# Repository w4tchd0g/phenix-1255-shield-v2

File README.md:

# phenix-1255-shield-v2

Expansion board (shield) for the NXP **FRDM-MCXN947** development board, built around the Semtech **SX1255** RF transceiver (TX 440 MHz, RX 430 MHz).

Together with the firmware it turns the FRDM board into a multimode SDR transceiver for base stations: TETRA today, DMR, FM and more modes planned. The I/Q samples are streamed to a host over HS USB or Ethernet.

This board is the hardware part of [phenix-1255-sw](https://github.com/w4tchd0g/phenix-1255-sw). It is **revision V2** of [phenix-1255-shield](https://github.com/w4tchd0g/phenix-1255-shield), see [Changes from V1](#changes-from-v1). Both are modified versions of [Phenix-1255-HW](https://github.com/labdvm/Phenix-1255-HW) by Z32IT ([@labdvm](https://github.com/labdvm)), see [Changes from Phenix-1255-HW](#changes-from-phenix-1255-hw).

> **Status:** V2 design complete, not yet built. The schematic passes ERC without errors, the PCB passes DRC without errors and without unrouted connections. The changes from V1 are checked by ERC/DRC and by calculation only; they still need a test on real boards. The Gerber, BOM and position files for JLCPCB and PCBWay are in [`production/`](#fabrication). Before the first power-up, read the [bring-up checklist](#bring-up-checklist).

## Preview

| Top | Bottom |
|---|---|
|  |  |

## Changes from V1

V2 continues [phenix-1255-shield](https://github.com/w4tchd0g/phenix-1255-shield) (V1). The circuit concept, the MCU pin assignment and the board outline are unchanged, so V1 firmware runs on V2 without changes (V2 also reports [hardware ID 0](#assembly-notes)). The changes (2026-11) are:

**RF front end**

- **RX SAW filter:** Tai-Saw TA1651A (428 MHz, passband 420–436 MHz, 3.0 × 3.0 mm, LCSC C5224551) instead of the Tai-Saw TA0655A (430 MHz, 4 MHz passband). JLCPCB places it; the TA0655A had to be soldered by hand. It rejects ≥ 45 dB below 400 MHz and above 470 MHz, but only about 2 dB more than in the passband at 439–440 MHz (the upper edge), so it does not reject the TX signal; for duplex operation an external duplexer at J5/J6 provides the TX/RX isolation.
- **Matching networks recalculated with the layout parasitics:** the short tracks and pads at the 100 Ω and 200 Ω nodes add about 1.2 pF each. **C13 = 2.2 pF** instead of 3.6 pF (TX return loss 40.6 dB instead of 14.6 dB) and **L3 = 43 nH** instead of 68 nH (RX match centred on the expected 6–8 pF at RF_IN instead of 5.24 pF). See [RF matching networks](#rf-matching-networks).
- **SMA jacks:** vertical through-hole jacks Kinghelm KH-SMA-KE-Z (gold-plated, LCSC C504007) instead of the hybrid land pattern for either a vertical SMD jack (TE CONSMA001-SMD-G) or an edge-mount jack (Samtec SMA-J-P-H-ST-EM1). The four GND posts are soldered through all four GND layers and take the tightening torque; JLCPCB solders the jacks. Return loss at the ports about 33–35 dB.
- **Jack position:** the jacks sit 0.64 mm further from the board edge (centre 5.04 mm from the edge), L1/D1 and L5/D8 1.27 mm further. FL2 sits as far from the bend of the RX line as C21.

**Power**

- **R20 (0 Ω) between QOD and VOUT of the PA load switch U2:** in V1, QOD was tied directly to VOUT. With R20 fitted the behaviour is the same as in V1 (VBAT3 is actively discharged while the PA is off). Without R20, VBAT3 floats like in Phenix-1255-HW. This allows testing whether the SX1255 tolerates the discharged VBAT3 (see [bring-up checklist](#bring-up-checklist)).

**PCB and assembly**

- **SX1255 exposed pad:** 9 thermal vias arranged as a cross instead of a 3 × 3 grid, so that the paste can be 4 regular squares (57 % of the land) instead of 8 irregular openings.
- **Fiducials:** three fiducials (FID1–FID3) for machine assembly.
- **TCXO:** Epson TG2016SMN (2.0 × 1.6 mm, LCSC C1987359) instead of the TG2520SMN (2.5 × 2.0 mm), which LCSC could not deliver. Same series and suffix (`38.4000M-MCGNNM3`: 38.4 MHz, 2.66–3.465 V, ±0.5 ppm from −40 to +85 °C, clipped sine) and the same pinout; only the land pattern is smaller (own footprint per the Epson datasheet). It sits at the position of the former TCXO, between the decoupling capacitors C5/C7 above and the coupling capacitor C10 below, with its own GND via like the capacitors.
- **Assembly:** JLCPCB now places FL2 and J5/J6 as well. Only the display and the FRDM headers are soldered by hand.
- **Ground stitching:** via fences adapted to the new positions, 319 GND vias.
- **Silkscreen:** `RX`/`TX` without the frequency, aligned reference designators, revision V2 in the title blocks.

**Documentation and scripts**

- `scripts/rf_calc.py` models the through-hole SMA launch (axisymmetric field solver) and includes the layout parasitics in the matching networks.
- `scripts/make_3d_models.py` generates the models of the KH-SMA-KE-Z, the TA1651A and the TG2016SMN. The SMA variant images and `scripts/sma_variant.py` are gone.
- The length of the longest RF line is corrected (38.9 mm, about 36° at 440 MHz).

## Changes from Phenix-1255-HW

The basic hardware concept comes from [labdvm/Phenix-1255-HW](https://github.com/labdvm/Phenix-1255-HW) (Copyright © Z32IT 2026, CERN-OHL-P-2.0). This project changes revision V2 of Phenix-1255-HW (not to be confused with revision V2 of this shield) as follows (2026-11):

**RF**

- **Antenna matching:** new matching networks. TX: an L-network transforms the 50 Ω of the LFCN-490+ to the 100 Ω optimum load of RFO_P (before: 100 pF straight to the filter). RX: 100 pF / 33 nH / 43 nH for the 200 Ω LNA input (before: 39 nH series, 82 nH shunt). See [RF matching networks](#rf-matching-networks).
- **RF connectors:** SMA instead of U.FL: vertical through-hole jacks (Kinghelm KH-SMA-KE-Z) at J5/J6. The four GND posts are soldered through all four GND layers, so the jacks take the tightening torque.
- **RX SAW filter:** Tai-Saw TA1651A (428 MHz, passband 420–436 MHz) instead of the Tai-Saw TA0655A (430 MHz, 4 MHz passband), so that JLCPCB can place it.
- **Port protection:** each SMA port has a 100 nH DC shunt and a low-capacitance TVS diode (before: 1 MΩ to GND). A BAV99 limiter protects the RX input of the SX1255.
- **PCB:** 4 layers instead of 2, with 50 Ω coplanar waveguides on a solid GND plane, via fences along the RF lines and a GND stitching grid, see [PCB](#pcb). No mounting holes.
- **Reference clock:** Epson TG2016SMN (2.0 × 1.6 mm) footprint only, TCXO AC-coupled to XTB through 10 nF (before: direct connection with 10 kΩ / 10 pF to GND).

**Power**

- **3.3 V regulator:** an ST LDK130M33R (SOT-23-5) replaces the Microchip MCP1703A (SOT-223). It runs directly from `+5v0`; the PTC fuse, the TVS array and the ferrite bead at the input are gone.
- **Supply split:** the LDO only supplies the RF part (SX1255, TCXO, PA load switch). Display, buttons and jumpers run from the FRDM 3.3 V rail. The 1 Ω series resistors in the SX1255 supply pins are gone. See [Power](#power).
- **PA supply switching:** an integrated load switch (TPS22917) replaces the P-channel MOSFET. The *bypass* solder jumper is gone.

**Digital interface and MCU pins**

- **`~PA_EN` pin:** moved from P2_4 to P1_23 (J9.23) for better routing.
- **Series resistors:** 33 Ω at the driving end of each SX1255 signal. NSS has a 10 kΩ pull-up, CK_IN and Q_IN are bridged and pulled down with one 10 kΩ resistor, `SX_RST` has no series resistor.
- **Hardware ID:** three solder jumpers (JP1–JP3, `HW_ID_0`…`HW_ID_2`) encode the board version, so that the firmware can support several hardware versions (up to 8). This board is **hardware ID 0** (all jumpers open).
- **Buttons:** Panasonic EVQ-Q2 instead of C&K PTS647. *OK* and *→* swapped pins: *OK* is now on P1_22 (J3.3), *→* on P4_12 (J4.1).
- **Status LEDs:** five instead of four; the new PA LED lights while the PA is powered. The LEDs on the GPIOs were reassigned: P0_14 green *OK* (before: red *Err*), P0_22 yellow *INFO* (before: *Warn*), P0_15 red *ERR* (before: green *Good*). 1 kΩ instead of 1.5 kΩ series resistors.
- **Display:** footprint with the module outline (DS1) instead of a 1×4 socket, without series resistors in SCL/SDA.

See [MCU pin assignment](#mcu-pin-assignment) for the pins. The TX driver amplifier of the *V2 Plus* variant is not part of this design.

## Overview

| | |
|---|---|
| Base board | [NXP FRDM-MCXN947](https://www.nxp.com/design/design-center/development-boards-and-designs/FRDM-MCXN947) |
| Revision | V2 (2026-11-21), successor of [phenix-1255-shield](https://github.com/w4tchd0g/phenix-1255-shield) (V1) |
| EDA tool | KiCad 10 |
| Board size | 118 × 55 mm, R2 corners, 17 × 5 mm cutout (R1 corners) on the left edge for the Ethernet jack of the FRDM board |
| Stackup | 4 layers, 1.6 mm, JLCPCB JLC04161H-7628 |
| Assembly | all parts on the top side; JLCPCB places everything except the display and the FRDM headers (SMA jacks through hole, wave soldering) |
| Based on | [Phenix-1255-HW](https://github.com/labdvm/Phenix-1255-HW) by Z32IT (CERN-OHL-P-2.0), see [Changes from Phenix-1255-HW](#changes-from-phenix-1255-hw) |
| Shield template | FRDM-MCXN947 shield template from [wavenumber-eng/frdm-templates](https://github.com/wavenumber-eng/frdm-templates) (CC0): board outline, header placement and root schematic |

## Components

| Function | Part | Manufacturer |
|---|---|---|
| RF transceiver | SX1255IWLTRT (QFN-32, 5 × 5 mm) | Semtech |
| Reference clock | TG2016SMN 38.4000M-MCGNNM3, 38.4 MHz TCXO (2.0 × 1.6 mm, LCSC C1987359) | Epson |
| SAW filter 428 MHz (RX) | TA1651A (3.0 × 3.0 mm, LCSC C5224551) | Tai-Saw |
| Low-pass filter (TX) | LFCN-490+ | Mini-Circuits |
| RF connectors (TX, RX) | KH-SMA-KE-Z (SMA jack, vertical, through hole, gold-plated, LCSC C504007) | Kinghelm |
| ESD protection RF ports | PESD5V0F1BL | Nexperia |
| RX input limiter | BAV99 | Nexperia |
| LDO 3.3 V | LDK130M33R | ST |
| PA supply load switch | TPS22917LDBVR (active-low enable) | TI |
| Display | OLED 0.96″ 128×64, SSD1306, I²C, pin order GND/VDD/SCL/SDA (module with on-board pull-ups) | – |
| Tactile switch (SPST-NO, 6.5 × 6 mm, SMD), 3× | EVQ-Q2Y03W | Panasonic |
| Status LEDs 0603, 5× (PWR, PA, OK, INFO, ERR) | 19-21/GHC-YR1S2/4T (green), 19-21/Y2C-CP1Q2B/4T (yellow), 19-21/R6C-FP1Q2L/4T (red) | Everlight |
| Hardware ID, 3× | solder jumper, open (hardware ID 0) | – |
| Headers to the FRDM board | Samtec SSQ (from the template) | Samtec |

Passives are 0603 (resistors UNI-ROYAL `0603WAF…`, capacitors Samsung/Murata/Yageo, RF inductors Murata `LQW18AN…`). The manufacturer part numbers are stored in the `MPN` field of the symbols, the JLCPCB/LCSC part numbers in the `LCSC` field. The display and the headers are not in the JLCPCB library.

## Circuit

### Power

| Net | Source | Loads |
|---|---|---|
| `+5v0` | FRDM header J3.10 | LDO input |
| `+3.3V_LDO` | LDO on the shield (enable tied to `+5v0`) | SX1255 VBAT1/VBAT2, TCXO, load switch input, PWR LED |
| `VBAT3` | load switch, controlled by `~PA_EN` | SX1255 VBAT3 (PA supply), PA LED |
| `+3v3` | FRDM header (J3.4, J3.8, J9.21, J8.1) | display, buttons, HW-ID jumpers, `~PA_EN` pull-up |

The RF part runs from its own low-noise LDO. Only the MCU-side parts use the FRDM 3.3 V rail.

`~PA_EN` is **active low** and pulled up to `+3v3` with 100 kΩ, so the PA supply stays off until the firmware drives the pin low. The load switch uses quick output discharge: QOD connects to VOUT through R20 (0 Ω), so VBAT3 is discharged while the PA is off. Without R20, VBAT3 floats when the switch is off. CT is left open, which gives the fastest turn-on.

### RF

- **TX:** SX1255 RFO_P → matching network (100 pF / 2.2 pF / 18 nH) → LFCN-490+ low-pass → SMA **J5 (TX)**. RFO_N is AC-coupled to GND.
- **RX:** SMA **J6 (RX)** → TA1651A SAW filter (passband 420–436 MHz) → matching network (100 pF / 33 nH / 43 nH) → SX1255 RFI, with a BAV99 limiter at the RFI pin. The TA1651A rejects ≥ 45 dB below 400 MHz (e.g. TETRA 380–395 MHz) and above 470 MHz, but 439–440 MHz lies on its upper edge (about 3.5–6 dB in total, 2–4 dB more than in the passband), so it does not reject the TX signal; for duplex operation an external duplexer connected to J5/J6 provides the TX/RX isolation.
- **SMA ports:** each port has a 100 nH DC shunt to GND (L1/L5) and a low-capacitance TVS diode (D1/D8). They need no further matching: return loss ≥ 24 dB, about 33–35 dB together with the through-hole launch of the jack (about 0.64 pF, which partly cancels the 100 nH).
- **RF lines:** 50 Ω coplanar waveguide with ground (CPWG) on F.Cu over the solid GND plane In1, 0.30 mm track, 0.30 mm gap (0.20 mm inside the SX1255 courtyard). A field-solver check gives about 52 Ω with solder mask, i.e. a return loss of about 33 dB. The lines are electrically short (longest RF net 38.9 mm ≈ 36° at 440 MHz).
- **Reference clock:** the 38.4 MHz TCXO drives XTB through 10 nF, XTA is left open (TCXO connection per the datasheet). 38.4 MHz is above the specified FXOSC range of the SX1255 (32 / 36 / 36.864 MHz min/typ/max, datasheet Rev. 3.0, table 5). It has been **tested and works**; keep in mind that it is outside the specification. All frequencies derived from FXOSC (PLL step, I/Q sample rate) scale with 38.4 MHz.

`scripts/rf_calc.py` reproduces all RF numbers in this README (CPWG impedance, SMA launch, port shunts, matching networks). It runs with the standard library; the field solver part also needs numpy and scipy (`pip install numpy scipy`).

### RF matching networks

The networks adapt the SX1255 impedances to the 50 Ω of the LFCN-490+ and the TA1651A. They are based on the SX1255 datasheet (Rev. 3.0) and on separate front-end design notes (*SX1255 RF front end: TX 440 MHz / RX 430 MHz*, not in this repository). The values include the parasitic capacitance of the layout at the high-impedance nodes (tracks and pads, estimated with the field solver) and the ESL of C13. They are **start values**; the final tuning is done on the board with a VNA.

#### TX: 100 Ω → 50 Ω

```
RF_OP ──C14 100p──┬──L2 18n──► LFCN-490+ (50 Ω) ──► J5
                  │
               C13 2.2p
                  │
                 GND
RF_ON ──C15 100p── GND
```

The datasheet specifies an optimum load of **100 Ω differential** between RF_OP and RF_ON (section 3.4.4, peak output power +5 dBm). The output is used single-ended: C15 ties RF_ON to ground for RF, so RF_OP has to see 100 Ω. The low-pass L-network (Q = 1) transforms 50 Ω up to 100 Ω:

| Element | Calculated | Used |
|---|---|---|
| Shunt C | 3.62 pF | **C13 = 2.2 pF** (C0G, ±0.25 pF) + 1.20 pF layout (C13 node 0.71 pF, RFO_P node 0.49 pF) + ESL ≈ 3.42 pF |
| Series L | 18.09 nH | **L2 = 18 nH** (wirewound, ±2 %) |

C14 (100 pF) only blocks DC. With the values used, RF_OP sees 99.2 + j1.7 Ω at 440 MHz (return loss 40.6 dB, ≥ 23 dB from 400 to 480 MHz, ≥ 24.9 dB from 430 to 450 MHz within the component tolerances). The previous C13 = 3.6 pF ignored the layout capacitance and would give only 14.6 dB. The network adds 3.1 dB attenuation at the 2nd and 9.5 dB at the 3rd harmonic on top of the LFCN-490+.

**Tuning element: C13.** The output capacitance of RF_OP is not specified and appears in parallel with C13. Trim C13 for maximum output power at J5 (keep 1.8 / 2.0 / 2.4 pF at hand).

#### RX: 50 Ω → 200 Ω

```
J6 ──► TA1651A (50 Ω) ──C21 100p──L4 33n──┬────────┬────────┬──► RF_IN (200 Ω)
                                          │        │        │
                                        L3 43n   D4 BAV99  C_pin (LNA input)
                                          │        │        │
                                         GND      GND      GND
```

RF_IN is a common-gate LNA with an input impedance of 50 Ω or 200 Ω, selected with the bit LnaZin in RegRxAnaGain (section 3.6.2). The network is designed for **200 Ω** (see [Firmware notes](#firmware-notes)).

The ideal L-network at 430 MHz is a series L of 32.05 nH (**L4 = 33 nH**) and a shunt C of 3.21 pF at RF_IN. There is no shunt capacitor on the board: that capacitance comes from the RF_IN node itself (LNA input, BAV99, pads, track). It is larger than needed, and **L3 (43 nH)** compensates the excess (43 nH cancels 3.19 pF at 430 MHz). L3 also gives RF_IN a DC path to ground. The values used require a **total capacitance of 6.41 pF at RF_IN**. Expected: about 4.5 pF for the chip and its connection (implied by the reference values 39 nH / 82 nH without limiter), up to 3 pF for the BAV99 (Nexperia: ≤ 1.5 pF per diode, two in antiparallel) and 1.22 pF for the 7.3 mm track and the pads of this layout, i.e. about 6–8 pF. The datasheet does not specify the LNA input capacitance, so this remains the critical assumption of the RX match (L3 was 68 nH before, designed for 5.24 pF):

| Total capacitance at RF_IN | Return loss at 430 MHz | Best match at |
|---|---|---|
| 5.0 pF | 8.8 dB | 494 MHz |
| 5.5 pF | 12.0 dB | 470 MHz |
| 6.0 pF | 17.9 dB | 449 MHz |
| **6.41 pF** | **29.2 dB** | **433 MHz** |
| 7.0 pF | 17.2 dB | 414 MHz |
| 7.5 pF | 11.7 dB | 398 MHz |
| 8.0 pF | 8.6 dB | 385 MHz |

With the nominal value the return loss is ≥ 20 dB from 420 to 446 MHz, which covers the 420–436 MHz passband of the TA1651A. The 0.39 pF of the node between C21 and L4 is included.

**Tuning element: L3.** For a match at 430 MHz: 5 pF → 77 nH, 6 pF → 49 nH, 7 pF → 36 nH, 8 pF → 29 nH (keep 39 / 47 nH at hand). Procedure (from the design notes): before the TA1651A is fitted, solder a coax pigtail to its output pad (pin 5) and measure S11 towards the SX1255. If the minimum is above 430 MHz, increase L3; if it is below, decrease L3. Adjust the depth with L4 (27 / 33 / 39 nH). Target S11 ≤ −10 dB, then optimise for best sensitivity.

### Digital interface

All signals between the SX1255 and the headers have 33 Ω series resistors at the driving end: next to the SX1255 for its outputs (`CK_OUT`, `I_OUT`, `MISO`, `DIO0..3`), next to the headers for the MCU outputs (`SCK`, `MOSI`, `NSS`, `I_IN`). NSS has a 10 kΩ pull-up to `+3.3V_LDO`. CK_IN and Q_IN are unused inputs: pins 11 and 12 are bridged next to the SX1255 and pulled down together with one 10 kΩ resistor (R4). Q_OUT and XTA are not connected.

## MCU pin assignment

| Net | Header | FRDM signal | Function |
|---|---|---|---|
| `SCK` | J2.12 | P0_25 / FC1_SCK | SX1255 SPI |
| `MISO` | J2.10 | P0_26 / FC1_SDI | SX1255 SPI |
| `MOSI` | J2.8 | P0_24 / FC1_SDO | SX1255 SPI |
| `NSS` | J1.16 | P0_31 | SX1255 SPI chip select (GPIO) |
| `SX_RST` | J1.6 | P0_29 | SX1255 reset (active high) |
| `DIO0` | J2.2 | P0_28 | SX1255 DIO0 |
| `DIO1` | J1.10 | P0_30 / P4_13 | SX1255 DIO1 |
| `DIO2/WS` | J1.13 | P3_19 / SAI1_RX_FS | SX1255 DIO2, I/Q word select |
| `DIO3` | J2.13 | P0_19 | SX1255 DIO3 |
| `CK_OUT` | J1.9 | P3_18 / SAI1_RX_BCLK | I/Q bit clock from SX1255 |
| `I_OUT` | J1.15 | P3_21 / SAI1_RXD0 | I/Q data SX1255 → MCU |
| `I_IN` | J1.5 | P3_20 / SAI1_TXD0 | I/Q data MCU → SX1255 |
| `~PA_EN` | J9.23 | P1_23 / EZH_LCD_RD | PA supply enable, active low |
| `SDA` | J2.17 | P1_0 | Display I²C |
| `SCL` | J2.15 | P1_1 | Display I²C |
| `BTN_0` | J3.1 | P2_0 | Button S1 (`<--`) |
| `BTN_1` | J3.3 | P1_22 | Button S2 (`OK`) |
| `BTN_2` | J4.1 | P4_12 / P0_21 | Button S3 (`-->`) |
| `LED_0` | J4.6 | P0_14 | LED OK (green) |
| `LED_1` | J4.8 | P0_22 | LED INFO (yellow) |
| `LED_2` | J4.10 | P0_15 (solder jumper SJ8 1-2, FRDM default) | LED ERR (red) |
| `HW_ID_0` | J9.5 | P1_19 / EZH_LCD_D15_CAMERA_RST | Hardware ID bit 0 |
| `HW_ID_1` | J9.12 | P3_4 | Hardware ID bit 1 |
| `HW_ID_2` | J9.11 | P3_5 | Hardware ID bit 2 |

Where the template lists two MCU pins (e.g. `P0_15 / P2_0`), the FRDM board routes the header pin to one of them via a solder jumper or resistor option. The pins above are the defaults from the FRDM-MCXN947 user manual (UM12018 Rev. 2.0). Some MCU pins also reach a second header on the FRDM board; on this shield the second pin is always left unconnected:

- P2_0 (`BTN_0`, J3.1) also goes to J9.25 (R167). It only reaches J4.10 if SJ8 is changed to 2-3, which would short `BTN_0` and `LED_2`. **Leave SJ8 on the FRDM board in its default position 1-2.**
- P1_22 (`BTN_1`, J3.3) also goes to J9.24.
- P1_23 (`~PA_EN`, J9.23) also goes to J1.8 (SJ1 1-2, default).

### Firmware notes

- **Buttons and HW-ID jumpers** switch to `+3v3` and have no external pull-downs. Enable the **internal pull-downs** on `BTN_x` and `HW_ID_x`. A pressed button or a closed jumper reads as `1`.
- **LEDs** `LED_0..2` are active high (1 kΩ to the LED). The PWR LED is always on, the PA LED lights while `VBAT3` is powered.
- **`SX_RST`** must stay **floating** in normal operation, as required by the SX1255 datasheet. Configure the GPIO as an input without pull resistor and drive it high only to reset.
- **`~PA_EN`**: drive it low to power the PA, drive it high or release it to switch the PA off.
- **LNA input impedance**: keep LnaZin (RegRxAnaGain, register 0x0C bit 0, reset value 1) at 1 = 200 Ω. The RX matching is designed for it; 50 Ω detunes the RX input.
- **I/Q interface**: SAI1 receives with the bit clock and frame sync from the SX1255; the transmitter has to run synchronously to the receiver.
- **Reference clock**: FXOSC is 38.4 MHz, not the 36 MHz of the datasheet examples. Calculate PLL and sample-rate settings with 38.4 MHz.

## PCB

### Stackup

JLCPCB JLC04161H-7628, 1.6 mm, 4 layers:

| Layer | Use | Dielectric to next layer |
|---|---|---|
| F.Cu | signals and RF (CPWG), GND fill | 0.21 mm prepreg 7628, εr 4.4 |
| In1.Cu | solid GND plane, no routing | 1.065 mm core, εr 4.6 |
| In2.Cu | power plane (`+3v3`, `+3.3V_LDO` and `+5v0` areas), GND below the RF section | 0.21 mm prepreg 7628, εr 4.4 |
| B.Cu | signals (SPI, DIO, SDA), GND fill | – |

The RF section has no vias in the signal path and no tracks on the inner layers or B.Cu. The GND layers are tied together with via fences along the RF lines and a stitching grid; the SX1255 exposed pad has 9 thermal vias arranged as a cross, with 4 square paste openings (57 % of the land) between them. Three fiducials sit in the corners. Design minimums: 0.15 mm track and clearance, 0.3 mm drill, 0.5 mm via diameter (vias used: 0.6 / 0.3 mm and 0.8 / 0.4 mm).

## Fabrication

Production files are in `production/`:

- `production/phenix-1255-shield-v2-gerber.zip` – upload this to JLCPCB or PCBWay (Gerber X1, Protel extensions, Excellon drill, PTH and NPTH separate).
- `production/gerber/` – the same files unpacked, plus the drill maps.
- `production/phenix-1255-shield-v2-bom.csv` and `production/phenix-1255-shield-v2-cpl.csv` – BOM and position file for JLCPCB assembly (see [Assembly notes](#assembly-notes)).

Order settings:

- **JLCPCB:** 4 layers, 1.6 mm, stackup **JLC04161H-7628** (the RF lines are calculated for it), 1 oz outer copper.
- **PCBWay:** 4 layers, 1.6 mm, 1 oz outer copper. The standard stackup is not guaranteed to match, so specify the [stackup](#stackup) in the order remark: layer order F.Cu (`.gtl`), In1.Cu (`.g1`), In2.Cu (`.g2`), B.Cu (`.gbl`); 0.21 mm prepreg 7628 between F.Cu and In1.Cu. The 50 Ω CPWG on F.Cu (0.30 mm track, 0.30 mm gap to the coplanar GND, reference In1.Cu) depends on that prepreg thickness.

Regenerate the files after every layout change:

```sh
./scripts/gerber.sh   # aborts if the DRC reports errors or unconnected items
./scripts/assembly.sh # BOM and position file for JLCPCB assembly
./scripts/render.sh   # updates the images in docs/img/
```

### Assembly notes

- All parts are on the top side. The SMA jacks J5/J6 are through hole (JLCPCB: wave soldering). Their posts stick out about 2.4 mm below the shield; check that nothing on the FRDM board underneath touches them.
- The display DS1 and the FRDM headers J1–J4, J8 and J9 are marked *Do not populate* in the schematic and on the PCB. `./scripts/assembly.sh` leaves them out of the BOM and the position file. Solder these parts by hand.
- JLCPCB assembly: upload `production/phenix-1255-shield-v2-bom.csv` and `production/phenix-1255-shield-v2-cpl.csv`. The position file contains rotation offsets for the SOT-23 packages (D4, U1, U2) and the SX1255 (IC1). **Check the orientation of D4, U1, U2, IC1, Y1 and FL2 (pin 1 = wide pad) in the JLCPCB placement preview** before ordering.
- Three fiducials (FID1–FID3, 1 mm copper in a 2 mm mask opening) sit in the top-right, bottom-right and bottom-left corners for machine assembly.
- This board is **hardware ID 0**: leave the jumpers JP1–JP3 open. Do not bridge them, otherwise the firmware detects a different hardware version.
- If the RX match is to be measured (see [RF matching networks](#rf-matching-networks)), order the first board without FL2 (set it to *Do not populate*).

## Bring-up checklist

These points cannot be checked on paper and need a measurement on the first board:

- **TX output:** check the single-ended output on RFO_P (no DC feed) against the Semtech reference design, and trim C13 for maximum output power.
- **RX match:** the match assumes 6.41 pF at RF_IN, which the datasheet does not specify. Measure S11 at the TA1651A output (FL2 pin 5) and adjust L3/L4.
- **PA supply:** confirm that the SX1255 tolerates VBAT3 switched off while VBAT1/VBAT2 are powered. With the PA off (`~PA_EN` high), measure VBAT3 against GND (e.g. at C19/C20): a few millivolts are fine; a clearly measurable voltage means current flows through the SX1255 into the 150 Ω discharge of U2. In that case remove R20, then VBAT3 floats.
- **SMA jacks:** the posts stick out about 2.4 mm below the shield. Check on the first board that nothing on the FRDM board touches them.
- **Reference clock:** 38.4 MHz is outside the SX1255 specification (tested and working, see [RF](#rf)).

## Project structure

```
phenix-1255-shield-v2/
├── phenix-1255-shield-v2.kicad_pro    # project file – open this one
├── phenix-1255-shield-v2.kicad_sch    # root schematic: FRDM headers, PWR_FLAGs
├── schematic.kicad_sch             # sub-sheet: SX1255, RF, power, UI
├── phenix-1255-shield-v2.kicad_pcb    # PCB
├── phenix-1255-shield-v2.kicad_dru    # custom design rules (RF, stitching)
├── phenix-1255-shield-v2.kicad_sym    # symbols from the template
├── sym-lib-table / fp-lib-table    # project libraries
├── empty.kicad_wks                 # drawing sheet
├── scripts/gerber.sh               # Gerber and drill files for JLCPCB and PCBWay
├── scripts/assembly.sh             # BOM and position file for JLCPCB assembly
├── scripts/jlc_csv.py              # helper for assembly.sh: JLCPCB column format, rotation offsets
├── scripts/render.sh               # renders the images in docs/img/
├── scripts/trim.py                 # helper for render.sh: crops the images to the board
├── scripts/rf_calc.py              # CPWG impedance, SMA launch and matching network calculation
├── scripts/make_3d_models.py       # generates the simplified 3D models in ext_parts/3d/
├── docs/img/                       # rendered PCB images
├── production/                     # Gerber, drill and assembly files (generated)
├── ext_parts/                      # project-specific symbols, footprints and 3D models
└── LICENSE                         # CERN-OHL-P-2.0
```

## Usage

1. Clone the repository.
2. Open `phenix-1255-shield-v2.kicad_pro` in KiCad 10.

The project-specific libraries are linked relative to the project via `${KIPRJMOD}`. Standard parts and their 3D models come from the KiCad 10 libraries that are installed with KiCad. Nothing else needs to be installed or configured.

**Notes:**

- According to NXP, the connectors in the template are 2–6 mil off from the exact Arduino positions. This is a design bug of the FRDM-MCXN947 itself; the shield still mates with the board.
- Always double-check the header IO assignments against the current FRDM-MCXN947 documentation before ordering boards.

## License

This project (schematics, PCB, the libraries in `ext_parts/`, scripts and documentation) is a modified version of [Phenix-1255-HW](https://github.com/labdvm/Phenix-1255-HW), Copyright © Z32IT 2026 (see [Changes from Phenix-1255-HW](#changes-from-phenix-1255-hw)), and is licensed under the [CERN Open Hardware Licence Version 2 – Permissive](LICENSE) (CERN-OHL-P-2.0), except for the third-party content listed below.

Third-party content:

- **Shield template** ([wavenumber-eng/frdm-templates](https://github.com/wavenumber-eng/frdm-templates), FRDM-MCXN947 KiCad template): board outline, header footprints and their placement, root schematic with the header symbols (`phenix-1255-shield-v2.kicad_sch`, `phenix-1255-shield-v2.kicad_sym`). [CC0 1.0](https://creativecommons.org/publicdomain/zero/1.0/)
- **Display footprint** `Display_128x64_096_I2C`: by TG9541 ([kicad-footprints](https://github.com/TG9541/kicad-footprints)), [CC0 1.0](https://creativecommons.org/publicdomain/zero/1.0/)
- **Standard parts:** footprints and 3D models from the KiCad libraries are referenced, not included (CC-BY-SA 4.0 with the KiCad library exception for designs).

Datasheets are not part of this repository; the `Datasheet` field of each part links to the manufacturer.

This source is distributed **WITHOUT ANY EXPRESS OR IMPLIED WARRANTY, INCLUDING OF MERCHANTABILITY, SATISFACTORY QUALITY AND FITNESS FOR A PARTICULAR PURPOSE**. Please see the CERN-OHL-P-2.0 for applicable conditions.

Source location: <https://github.com/w4tchd0g/phenix-1255-shield-v2>

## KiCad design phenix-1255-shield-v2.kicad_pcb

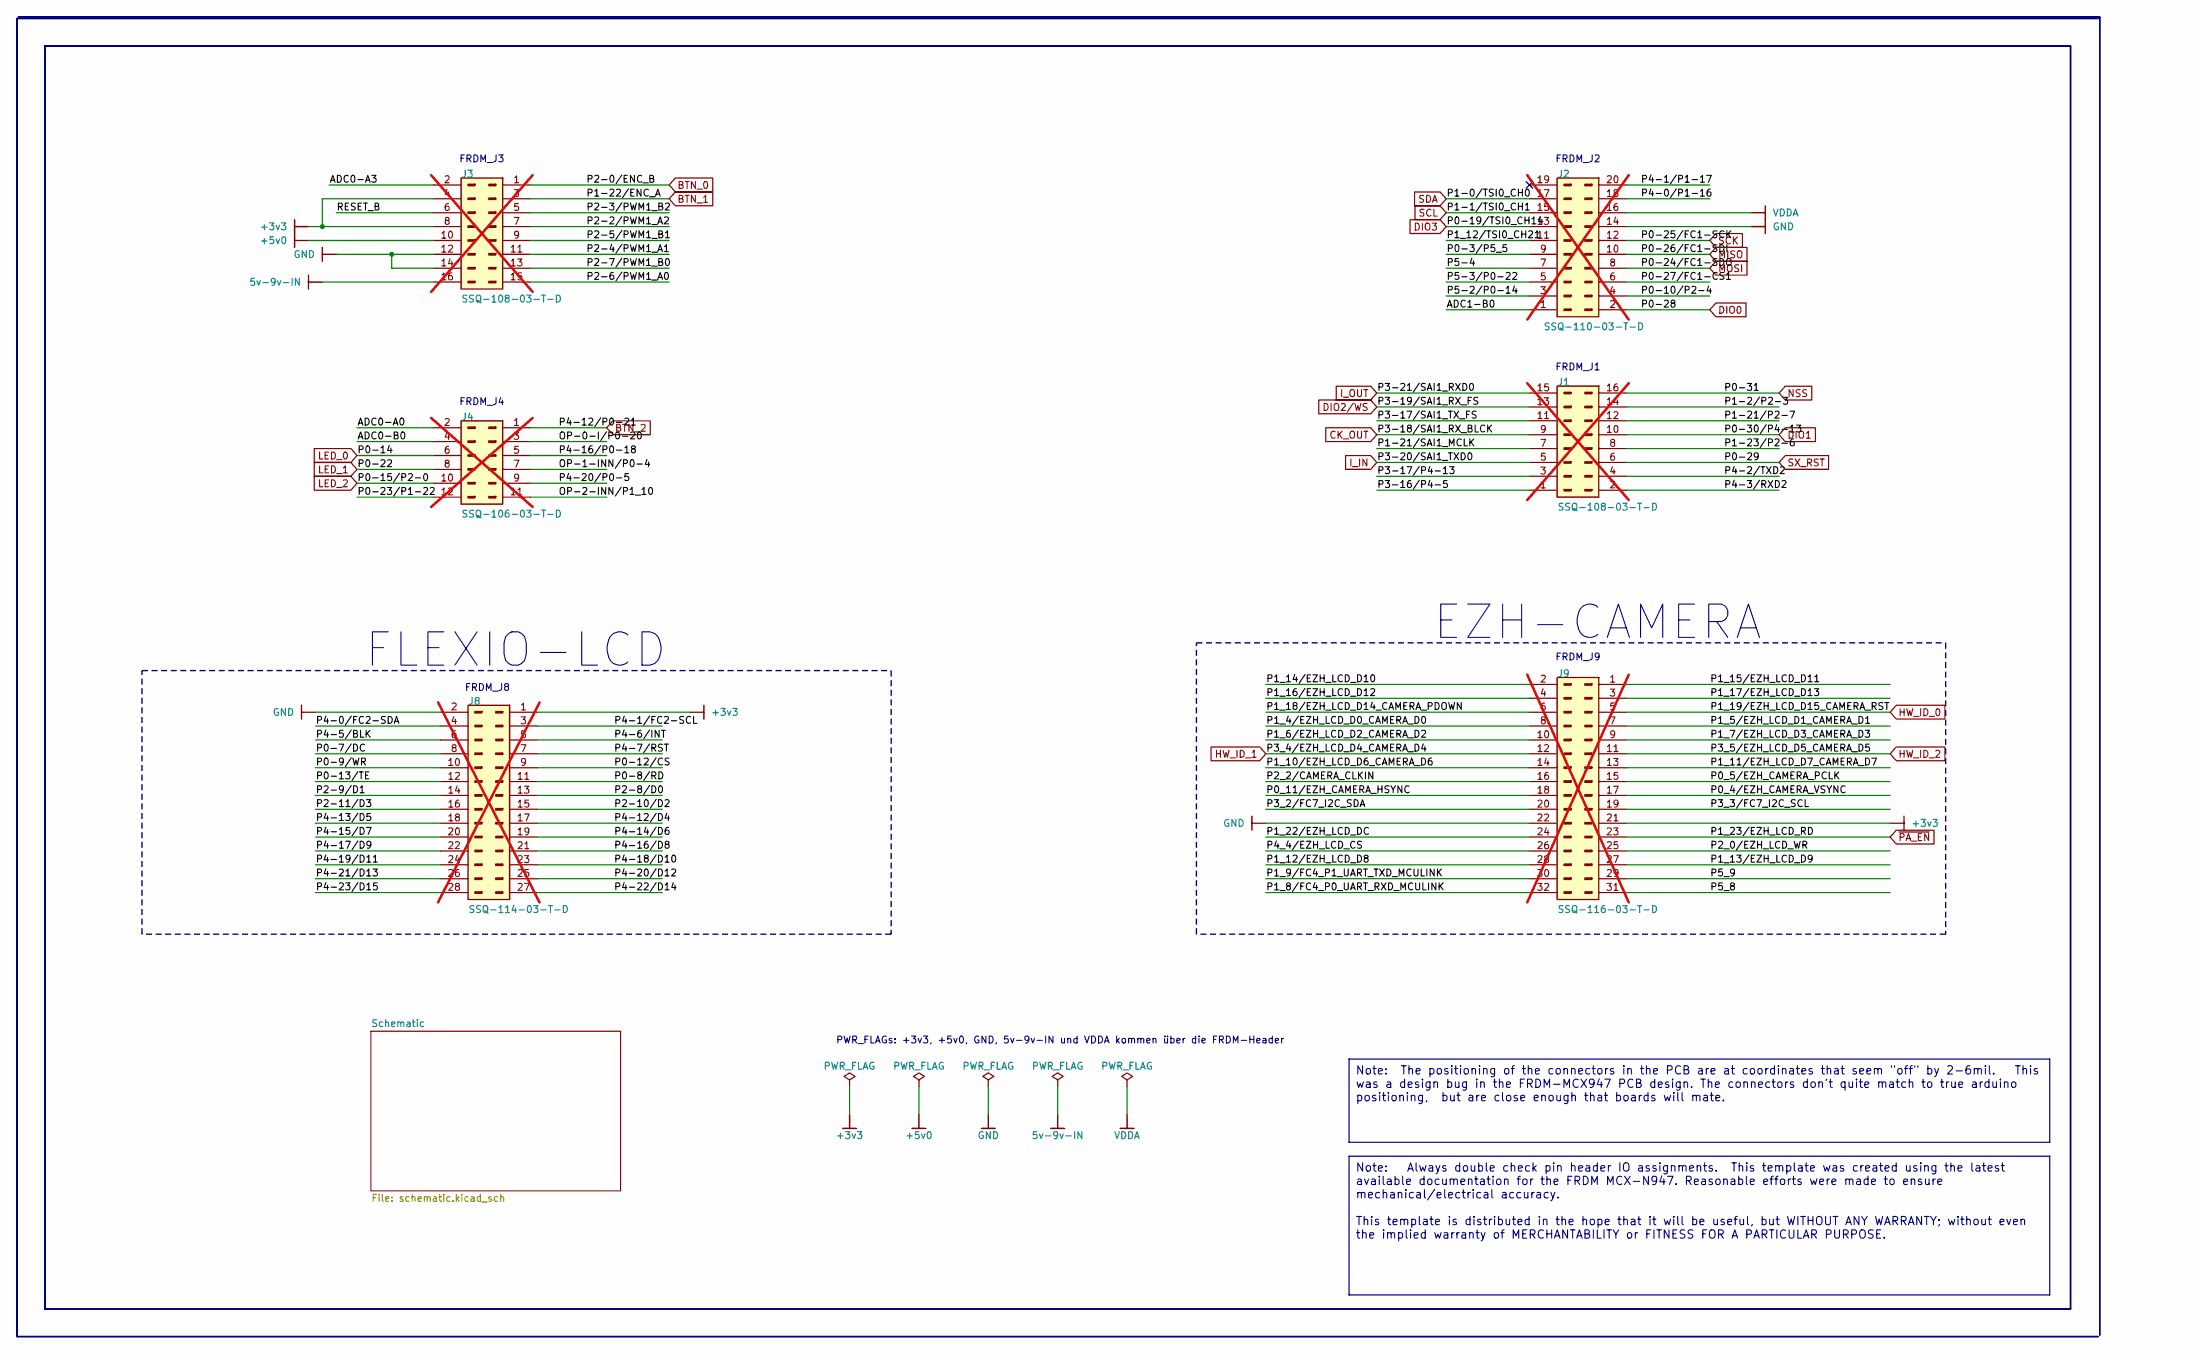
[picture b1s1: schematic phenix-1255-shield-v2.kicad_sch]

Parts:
J1, J3: SSQ-108-03-T-D; MANUFACTURER PART NUMBER SSQ-108-03-T-D; not fitted
J2: SSQ-110-03-T-D; MANUFACTURER PART NUMBER SSQ-110-23-T-D; not fitted
J4: SSQ-106-03-T-D; MANUFACTURER PART NUMBER SSQ-106-03-T-D; not fitted
J8: SSQ-114-03-T-D; MANUFACTURER PART NUMBER SSQ-114-03-T-D; not fitted
J9: SSQ-116-03-T-D; MANUFACTURER P/N SSQ-116-03-T-D; not fitted

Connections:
5v-9v-IN: J3.16
+3v3: J3.4, J3.8, J8.1, J9.21; also elsewhere on the board
+5v0: J3.10; also elsewhere on the board
/ADC0-A0: J4.2
/ADC0-A3: J3.2
/ADC0-B0: J4.4
/ADC1-B0: J2.1
/OP-0-I/P0-20: J4.3
/OP-1-INN/P0-4: J4.7
/OP-2-INN/P1_10: J4.11
/P0-3/P5_5: J2.9
/P0-7/DC: J8.8
/P0-8/RD: J8.11
/P0-9/WR: J8.10
/P0-10/P2-4: J2.4
/P0-12/CS: J8.9
/P0-13/TE: J8.12
/P0-23/P1-22: J4.12
/P0-27/FC1-CS1: J2.6
/P0_4/EZH_CAMERA_VSYNC: J9.17
/P0_5/EZH_CAMERA_PCLK: J9.15
/P0_11/EZH_CAMERA_HSYNC: J9.18
/P1-2/P2-3: J1.14
/P1-21/P2-7: J1.12
/P1-21/SAI1_MCLK: J1.7
/P1-23/P2-6: J1.8
/P1_4/EZH_LCD_D0_CAMERA_D0: J9.8
/P1_5/EZH_LCD_D1_CAMERA_D1: J9.7
/P1_6/EZH_LCD_D2_CAMERA_D2: J9.10
/P1_7/EZH_LCD_D3_CAMERA_D3: J9.9
/P1_8/FC4_P0_UART_RXD_MCULINK: J9.32
/P1_9/FC4_P1_UART_TXD_MCULINK: J9.30
/P1_10/EZH_LCD_D6_CAMERA_D6: J9.14
/P1_11/EZH_LCD_D7_CAMERA_D7: J9.13
/P1_12/EZH_LCD_D8: J9.28
/P1_12/TSI0_CH21: J2.11
/P1_13/EZH_LCD_D9: J9.27
/P1_14/EZH_LCD_D10: J9.2
/P1_15/EZH_LCD_D11: J9.1
/P1_16/EZH_LCD_D12: J9.4
/P1_17/EZH_LCD_D13: J9.3
/P1_18/EZH_LCD_D14_CAMERA_PDOWN: J9.6
/P1_22/EZH_LCD_DC: J9.24
/P2-2/PWM1_A2: J3.7
/P2-3/PWM1_B2: J3.5
/P2-4/PWM1_A1: J3.11
/P2-5/PWM1_B1: J3.9
/P2-6/PWM1_A0: J3.15
/P2-7/PWM1_B0: J3.13
/P2-8/D0: J8.13
/P2-9/D1: J8.14
/P2-10/D2: J8.15
/P2-11/D3: J8.16
/P2_0/EZH_LCD_WR: J9.25
/P2_2/CAMERA_CLKIN: J9.16
/P3-16/P4-5: J1.1
/P3-17/P4-13: J1.3
/P3-17/SAI1_TX_FS: J1.11
/P3_2/FC7_I2C_SDA: J9.20
/P3_3/FC7_I2C_SCL: J9.19
/P4-0/FC2-SDA: J8.4
/P4-0/P1-16: J2.18
/P4-1/FC2-SCL: J8.3
/P4-1/P1-17: J2.20
/P4-2/TXD2: J1.4
/P4-3/RXD2: J1.2
/P4-5/BLK: J8.6
/P4-6/INT: J8.5
/P4-7/RST: J8.7
/P4-12/D4: J8.17
/P4-13/D5: J8.18
/P4-14/D6: J8.19
/P4-15/D7: J8.20
/P4-16/D8: J8.21
/P4-16/P0-18: J4.5
/P4-17/D9: J8.22
/P4-18/D10: J8.23
/P4-19/D11: J8.24
/P4-20/D12: J8.25
/P4-20/P0-5: J4.9
/P4-21/D13: J8.26
/P4-22/D14: J8.27
/P4-23/D15: J8.28
/P4_4/EZH_LCD_CS: J9.26
/P5-2/P0-14: J2.3
/P5-3/P0-22: J2.5
/P5-4: J2.7
/P5_8: J9.31
/P5_9: J9.29
/RESET_B: J3.6
BTN_0: J3.1; also elsewhere on the board
BTN_1: J3.3; also elsewhere on the board
BTN_2: J4.1; also elsewhere on the board
CK_OUT: J1.9; also elsewhere on the board
DIO0: J2.2; also elsewhere on the board
DIO1: J1.10; also elsewhere on the board
DIO2/WS: J1.13; also elsewhere on the board
DIO3: J2.13; also elsewhere on the board
GND: J2.14, J3.12, J3.14, J8.2, J9.22; also elsewhere on the board
HW_ID_0: J9.5; also elsewhere on the board
HW_ID_1: J9.12; also elsewhere on the board
HW_ID_2: J9.11; also elsewhere on the board
I_IN: J1.5; also elsewhere on the board
I_OUT: J1.15; also elsewhere on the board
LED_0: J4.6; also elsewhere on the board
LED_1: J4.8; also elsewhere on the board
LED_2: J4.10; also elsewhere on the board
MISO: J2.10; also elsewhere on the board
MOSI: J2.8; also elsewhere on the board
NSS: J1.16; also elsewhere on the board
SCK: J2.12; also elsewhere on the board
SCL: J2.15; also elsewhere on the board
SDA: J2.17; also elsewhere on the board
SX_RST: J1.6; also elsewhere on the board
VDDA: J2.16
~PA_EN: J9.23; also elsewhere on the board

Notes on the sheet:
FRDM_J2
FRDM_J8
PWR_FLAGs: +3v3, +5v0, GND, 5v-9v-IN und VDDA kommen über die FRDM-Header
FRDM_J9
FRDM_J4
FRDM_J1
FLEXIO-LCD
FRDM_J3
EZH-CAMERA
Note: Always double check pin header IO assignments. This template was created using the latest available documentation for the FRDM MCX-N947. Reasonable efforts were made to ensure mechanical/electrical accuracy. This template is distributed in the hope that it will be useful, but WITHOUT ANY WARR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
Note: The positioning of the connectors in the PCB are at coordinates that seem "off" by 2-6mil. This was a design bug in the FRDM-MCX947 PCB design. The connectors don't quite match to true arduino positioning, but are close enough that boards will mate.

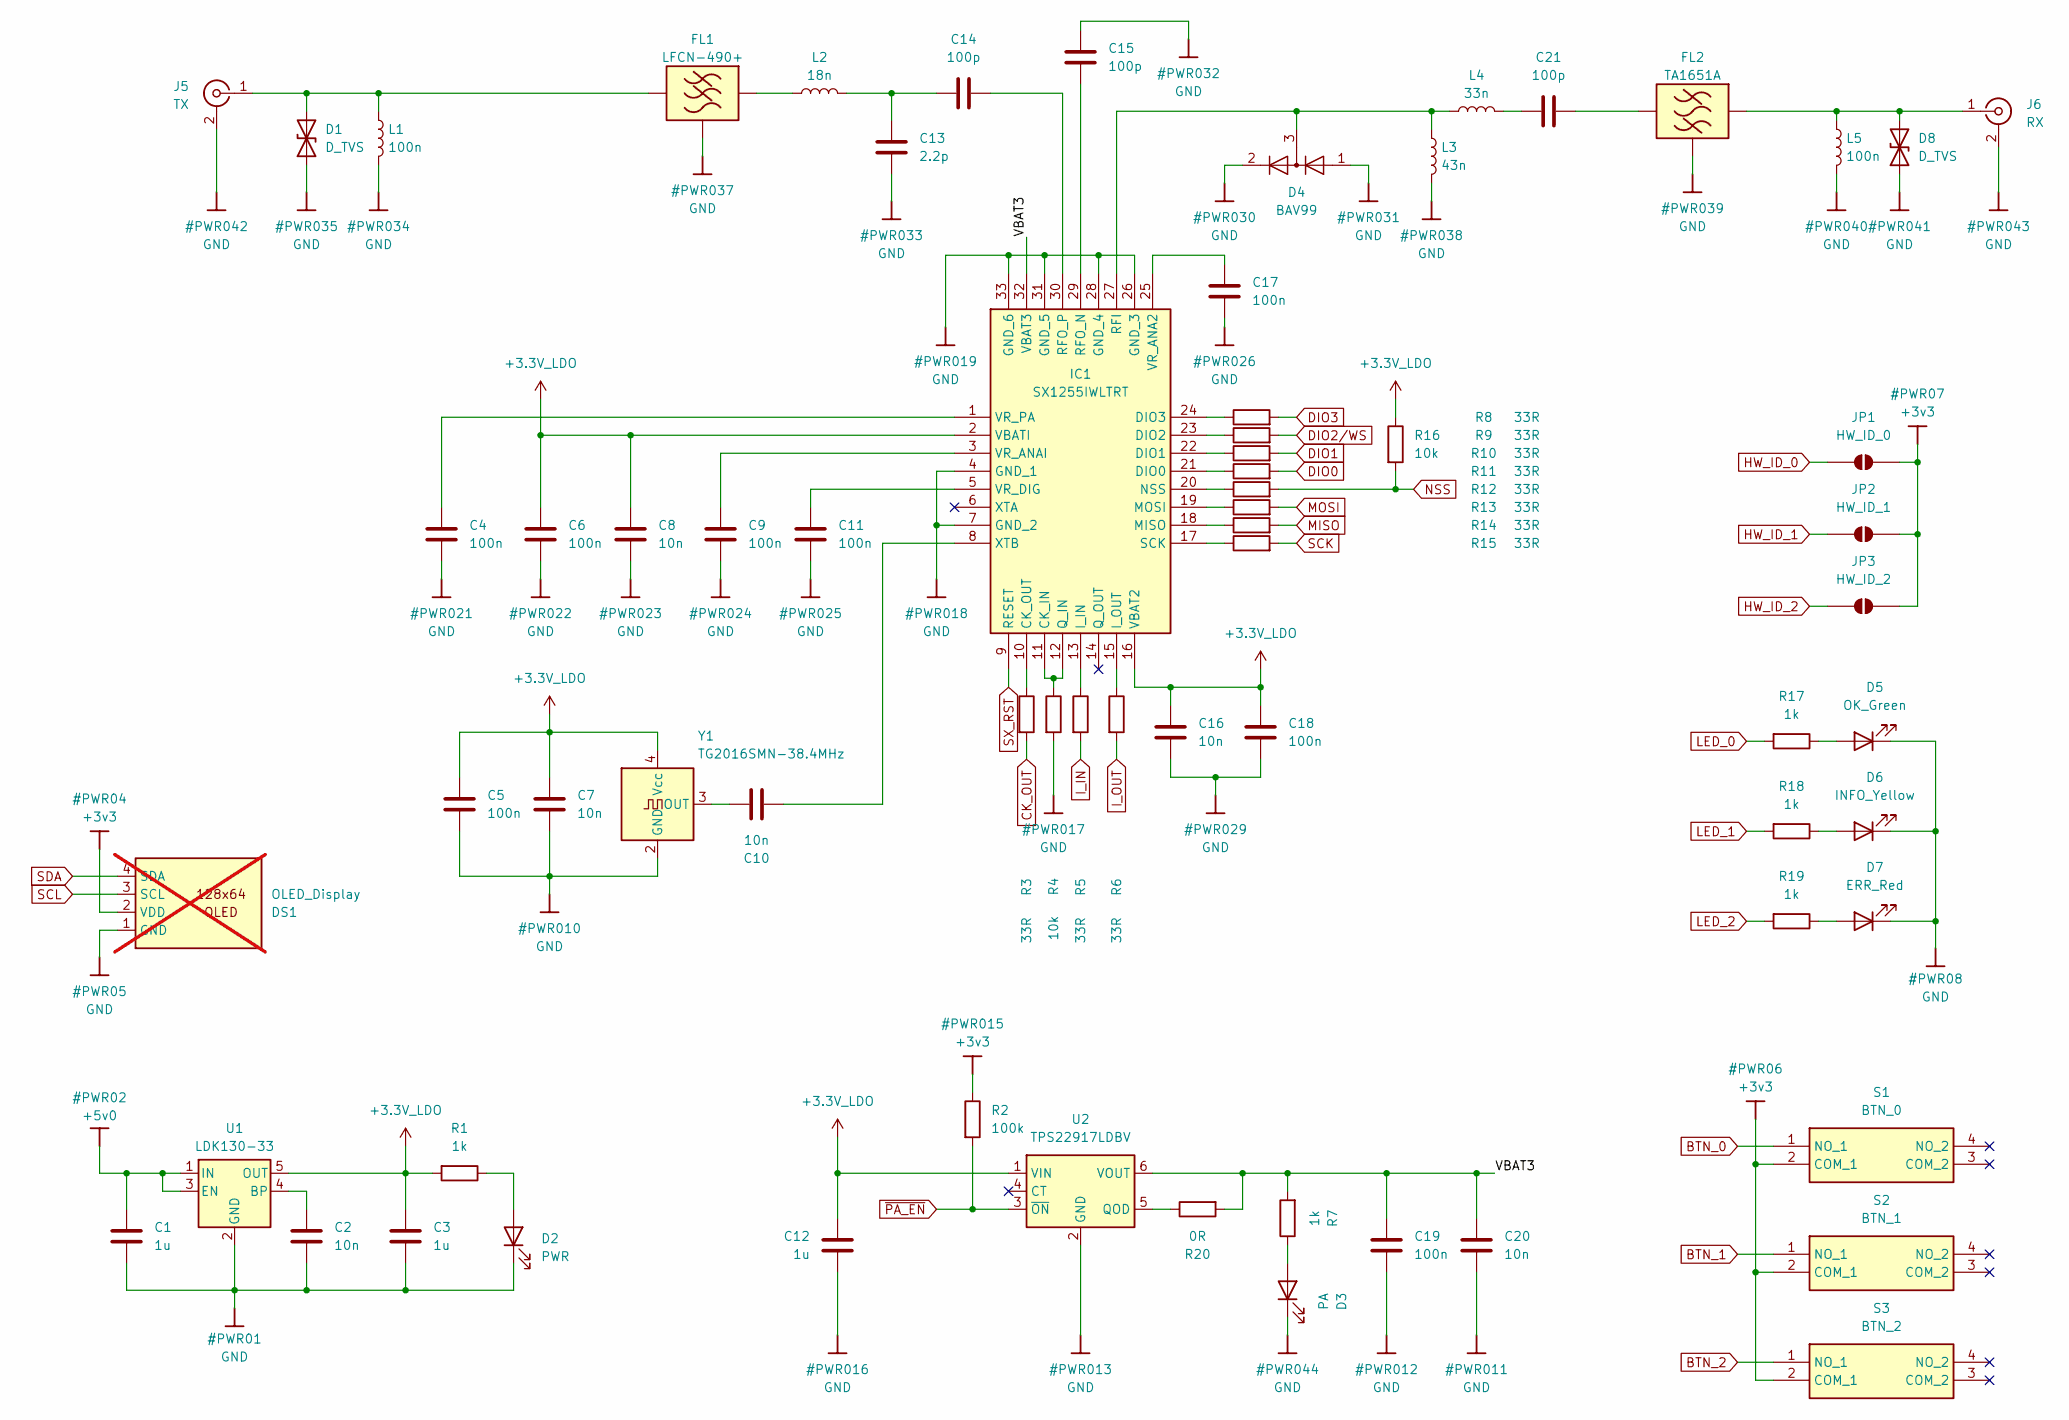
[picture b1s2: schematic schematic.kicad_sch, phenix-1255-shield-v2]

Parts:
C1, C3, C12: 1u; C_0603_1608Metric; MPN CL10A105KB8NNNC; LCSC C15849
C2, C7, C8, C10, C16, C20: 10n; C_0603_1608Metric; MPN GRM1885C1H103JA01J; LCSC C2215227
C4, C5, C6, C9, C11, C17, C18, C19: 100n; C_0603_1608Metric; MPN CC0603KRX7R9BB104; LCSC C14663
C13: 2.2p; C_0603_1608Metric; MPN CC0603CRNPO9BN2R2; LCSC C282246
C14, C15, C21: 100p; C_0603_1608Metric; MPN CL10C101JB8NNNC; LCSC C14858
D1, D8: D_TVS; D_SOD-882; MPN PESD5V0F1BL,315; LCSC C45961
D2: PWR; LED_0603_1608Metric; MPN 19-21/GHC-YR1S2/4T; LCSC C2986048
D3: PA; LED_0603_1608Metric; MPN 19-21/R6C-FP1Q2L/4T; LCSC C2986050
D4: BAV99; SOT-23; MPN BAV99,215; LCSC C2500
D5: OK_Green; LED_0603_1608Metric; MPN 19-21/GHC-YR1S2/4T; LCSC C2986048
D6: INFO_Yellow; LED_0603_1608Metric; MPN 19-21/Y2C-CP1Q2B/4T; LCSC C2986008
D7: ERR_Red; LED_0603_1608Metric; MPN 19-21/R6C-FP1Q2L/4T; LCSC C2986050
DS1: OLED_Display; Display_128x64_096_I2C; not fitted
FL1: LFCN-490+; LFCN490; MPN LFCN-490+; LCSC C3008205
FL2: TA1651A; MPN TA1651A; LCSC C5224551
IC1: SX1255IWLTRT; QFN50P500X500X80-33N-D; MPN SX1255IWLTRT; LCSC C89372
J5: TX; SMA_Kinghelm_KH-SMA-KE-Z_Vertical; MPN KH-SMA-KE-Z; LCSC C504007
J6: RX; SMA_Kinghelm_KH-SMA-KE-Z_Vertical; MPN KH-SMA-KE-Z; LCSC C504007
JP1: HW_ID_0; SolderJumper-2_P1.3mm_Open_RoundedPad1.0x1.5mm
JP2: HW_ID_1; SolderJumper-2_P1.3mm_Open_RoundedPad1.0x1.5mm
JP3: HW_ID_2; SolderJumper-2_P1.3mm_Open_RoundedPad1.0x1.5mm
L1, L5: 100n; L_0603_1608Metric; MPN LQW18ANR10G00D; LCSC C98088
L2: 18n; L_0603_1608Metric; MPN LQW18AN18NG00D; LCSC C86133
L3: 43n; L_0603_1608Metric; MPN LQW18AN43NG00D; LCSC C113126
L4: 33n; L_0603_1608Metric; MPN LQW18AN33NJ10D; LCSC C701171
R1, R7, R17, R18, R19: 1k; R_0603_1608Metric; MPN 0603WAF1001T5E; LCSC C21190
R2: 100k; R_0603_1608Metric; MPN 0603WAF1003T5E; LCSC C25803
R3, R5, R6, R8, R9, R10, R11, R12, R13, R14, R15: 33R; R_0603_1608Metric; MPN 0603WAF330JT5E; LCSC C23140
R4, R16: 10k; R_0603_1608Metric; MPN 0603WAF1002T5E; LCSC C25804
R20: 0R; R_0603_1608Metric; MPN 0603WAF0000T5E; LCSC C21189
S1: BTN_0; EVQQ2; MPN EVQQ2Y03W; LCSC C2828255
S2: BTN_1; EVQQ2; MPN EVQQ2Y03W; LCSC C2828255
S3: BTN_2; EVQQ2; MPN EVQQ2Y03W; LCSC C2828255
U1: LDK130-33; SOT-23-5; MPN LDK130M33R; LCSC C2969807
U2: TPS22917LDBV; SOT-23-6; MPN TPS22917LDBVR; LCSC C3235537
Y1: TG2016SMN-38.4MHz; TG2016SMN; MPN TG2016SMN 38.4000M-MCGNNM3; LCSC C1987359

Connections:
+3.3V_LDO: C3.1, C5.1, C6.1, C7.1, C8.1, C12.1, C16.1, C18.1, IC1.2 (VBATI), IC1.16 (VBAT2), R1.2, R16.1, U1.5 (OUT), U2.1 (VIN), Y1.4 (Vcc)
+3v3: DS1.2 (VDD), JP1.2 (B), JP2.2 (B), JP3.2 (B), R2.1, S1.2 (COM_1), S2.2 (COM_1), S3.2 (COM_1); also elsewhere on the board
+5v0: C1.1, U1.1 (IN), U1.3 (EN); also elsewhere on the board
/Schematic/VBAT3: C19.1, C20.1, IC1.32 (VBAT3), R7.2, R20.2, U2.6 (VOUT)
BTN_0: S1.1 (NO_1); also elsewhere on the board
BTN_1: S2.1 (NO_1); also elsewhere on the board
BTN_2: S3.1 (NO_1); also elsewhere on the board
CK_OUT: R3.2; also elsewhere on the board
DIO0: R11.2; also elsewhere on the board
DIO1: R10.2; also elsewhere on the board
DIO2/WS: R9.2; also elsewhere on the board
DIO3: R8.2; also elsewhere on the board
GND: C1.2, C2.2, C3.2, C4.2, C5.2, C6.2, C7.2, C8.2, C9.2, C11.2, C12.2, C13.2, C15.2, C16.2, C17.2, C18.2, C19.2, C20.2, D1.1 (A1), D2.1 (K), D3.1 (K), D4.1 (K), D4.2 (A), D5.1 (K), D6.1 (K), D7.1 (K), D8.1 (A1), DS1.1 (GND), FL1.2 (GROUND_1), FL1.4 (GROUND_2), FL2.1 (GND), FL2.3 (GND), FL2.4 (GND), FL2.6 (GND), IC1.4 (GND_1), IC1.7 (GND_2), IC1.26 (GND_3), IC1.28 (GND_4), IC1.31 (GND_5), IC1.33 (GND_6), J5.2 (Ext), J6.2 (Ext), L1.2, L3.2, L5.2, R4.2, U1.2 (GND), U2.2 (GND), Y1.2 (GND); also elsewhere on the board
HW_ID_0: JP1.1 (A); also elsewhere on the board
HW_ID_1: JP2.1 (A); also elsewhere on the board
HW_ID_2: JP3.1 (A); also elsewhere on the board
I_IN: R5.2; also elsewhere on the board
I_OUT: R6.2; also elsewhere on the board
LED_0: R17.2; also elsewhere on the board
LED_1: R18.2; also elsewhere on the board
LED_2: R19.2; also elsewhere on the board
MISO: R14.2; also elsewhere on the board
MOSI: R13.2; also elsewhere on the board
NSS: R12.2, R16.2; also elsewhere on the board
unnamed: C13.1, C14.1, L2.2
unnamed: C21.1, L4.2
unnamed: D1.2 (A2), FL1.3 (RF_OUT), J5.1 (In), L1.1
unnamed: D2.2 (A), R1.1
unnamed: D3.2 (A), R7.1
unnamed: D5.2 (A), R17.1
unnamed: D6.2 (A), R18.1
unnamed: D7.2 (A), R19.1
unnamed: D8.2 (A2), FL2.2 (IN), J6.1 (In), L5.1
unnamed: FL1.1 (RF_IN), L2.1
unnamed: C21.2, FL2.5 (OUT)
unnamed: IC1.11 (CK_IN), IC1.12 (Q_IN), R4.1
unnamed: IC1.10 (CK_OUT), R3.1
unnamed: IC1.21 (DIO0), R11.1
unnamed: IC1.22 (DIO1), R10.1
unnamed: IC1.23 (DIO2), R9.1
unnamed: IC1.24 (DIO3), R8.1
unnamed: IC1.13 (I_IN), R5.1
unnamed: IC1.15 (I_OUT), R6.1
unnamed: IC1.18 (MISO), R14.1
unnamed: IC1.19 (MOSI), R13.1
unnamed: IC1.20 (NSS), R12.1
unnamed: D4.3 (K), IC1.27 (RFI), L3.1, L4.1
unnamed: C15.1, IC1.29 (RFO_N)
unnamed: C14.2, IC1.30 (RFO_P)
unnamed: IC1.17 (SCK), R15.1
unnamed: C17.1, IC1.25 (VR_ANA2)
unnamed: C9.1, IC1.3 (VR_ANAI)
unnamed: C11.1, IC1.5 (VR_DIG)
unnamed: C4.1, IC1.1 (VR_PA)
unnamed: C10.2, IC1.8 (XTB)
unnamed: C2.1, U1.4 (BP)
unnamed: R20.1, U2.5 (QOD)
unnamed: C10.1, Y1.3 (OUT)
SCK: R15.2; also elsewhere on the board
SCL: DS1.3 (SCL); also elsewhere on the board
SDA: DS1.4 (SDA); also elsewhere on the board
SX_RST: IC1.9 (RESET); also elsewhere on the board
~PA_EN: R2.2, U2.3 (~ON); also elsewhere on the board

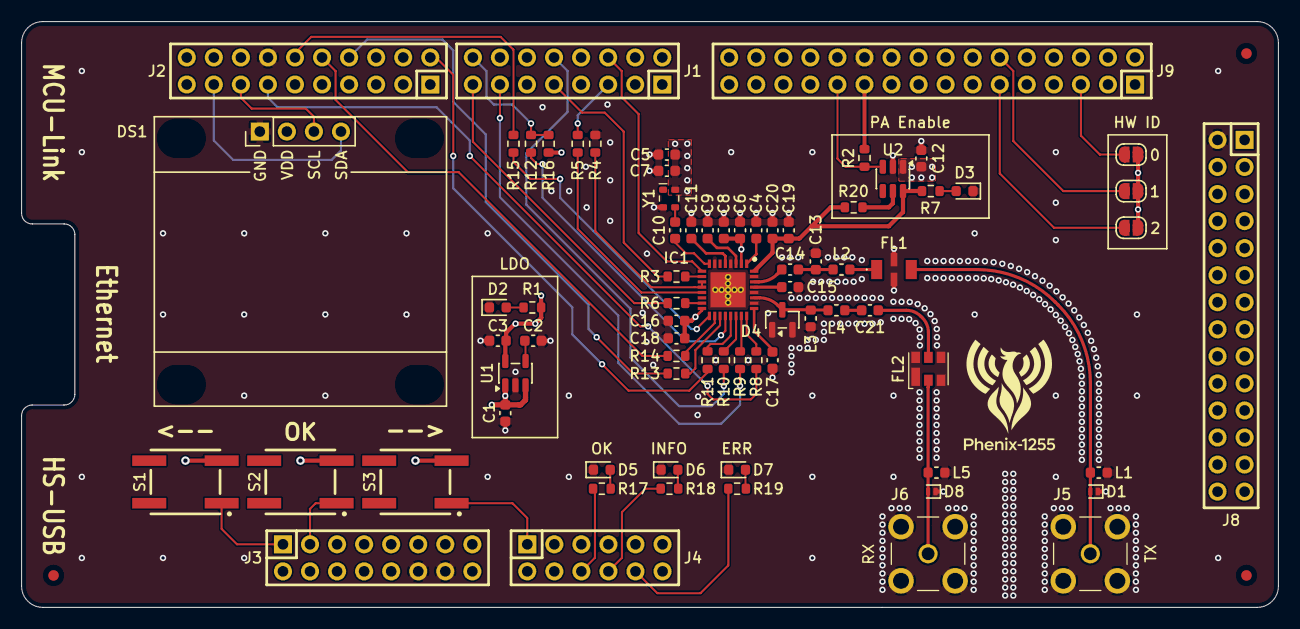
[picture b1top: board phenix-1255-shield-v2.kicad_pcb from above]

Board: 4 copper layers, 118.0 x 55.0 mm, 78 parts (0 on the bottom side), 63 nets.

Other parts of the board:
FID1, FID2, FID3: Fiducial_1mm_Mask2mm

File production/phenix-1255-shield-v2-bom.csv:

"Comment","Designator","Footprint","LCSC Part #"
"1u","C1,C3,C12","C_0603_1608Metric","C15849"
"10n","C2,C7,C8,C10,C16,C20","C_0603_1608Metric","C2215227"
"100n","C4,C5,C6,C9,C11,C17,C18,C19","C_0603_1608Metric","C14663"
"2.2p","C13","C_0603_1608Metric","C282246"
"100p","C14,C15,C21","C_0603_1608Metric","C14858"
"PESD5V0F1BL,315","D1,D8","D_SOD-882","C45961"
"19-21/GHC-YR1S2/4T","D2,D5","LED_0603_1608Metric","C2986048"
"19-21/R6C-FP1Q2L/4T","D3,D7","LED_0603_1608Metric","C2986050"
"BAV99,215","D4","SOT-23","C2500"
"19-21/Y2C-CP1Q2B/4T","D6","LED_0603_1608Metric","C2986008"
"LFCN-490+","FL1","LFCN490","C3008205"
"TA1651A","FL2","TA1651A","C5224551"
"SX1255IWLTRT","IC1","QFN50P500X500X80-33N-D","C89372"
"KH-SMA-KE-Z","J5,J6","SMA_Kinghelm_KH-SMA-KE-Z_Vertical","C504007"
"100n","L1,L5","L_0603_1608Metric","C98088"
"18n","L2","L_0603_1608Metric","C86133"
"43n","L3","L_0603_1608Metric","C113126"
"33n","L4","L_0603_1608Metric","C701171"
"1k","R1,R7,R17,R18,R19","R_0603_1608Metric","C21190"
"100k","R2","R_0603_1608Metric","C25803"
"33R","R3,R5,R6,R8,R9,R10,R11,R12,R13,R14,R15","R_0603_1608Metric","C23140"
"10k","R4,R16","R_0603_1608Metric","C25804"
"0R","R20","R_0603_1608Metric","C21189"
"EVQQ2Y03W","S1,S2,S3","EVQQ2","C2828255"
"LDK130M33R","U1","SOT-23-5","C2969807"
"TPS22917LDBVR","U2","SOT-23-6","C3235537"
"TG2016SMN 38.4000M-MCGNNM3","Y1","TG2016SMN","C1987359"

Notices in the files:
phenix-1255-shield-v2.kicad_pcb:
Based on Phenix-1255-HW, Copyright (c) Z32IT 2026
Modifications Copyright (c) w4tchd0g (DM5LF) 2026
